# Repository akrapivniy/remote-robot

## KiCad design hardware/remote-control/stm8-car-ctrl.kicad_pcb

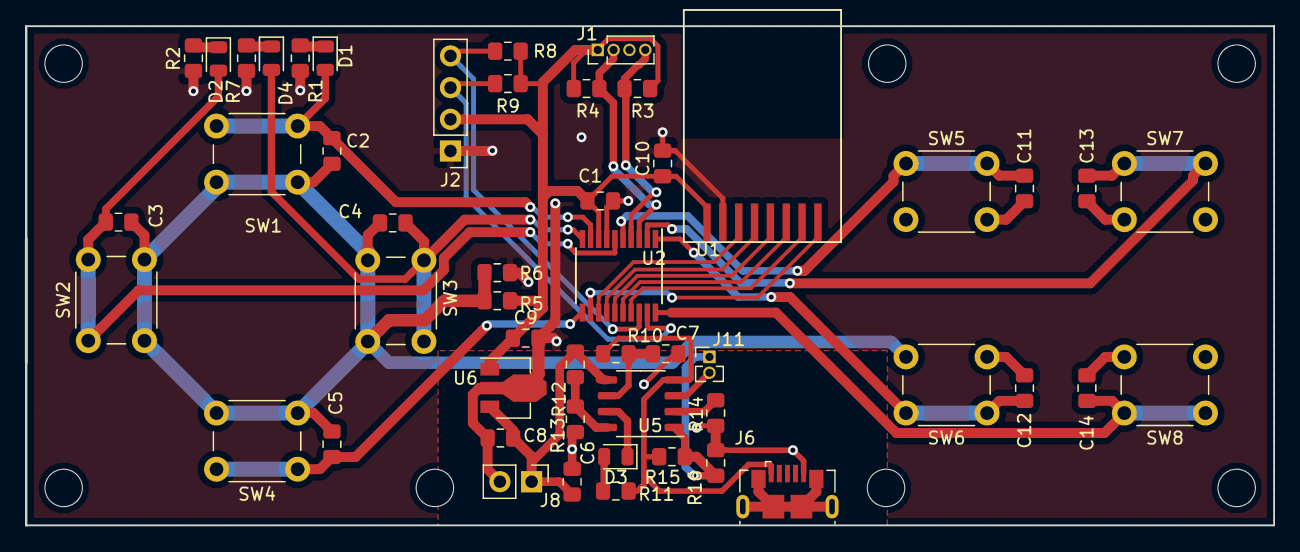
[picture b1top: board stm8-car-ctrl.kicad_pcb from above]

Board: 2 copper layers, 100.0 x 40.0 mm, 58 parts (0 on the bottom side), 32 nets.

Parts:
C1, C2, C3, C4, C5, C6, C7, C8, C9, C10, C11, C12, C13, C14: 100nF; C_0805_2012Metric_Pad1.15x1.40mm_HandSolder
D1, D2, D3, D4: LED; LED_0805_2012Metric
H1, H2, H3, H4, H6, H7, H8: MountingHole; MountingHole_3mm
J1: Prog; PinHeader_1x04_P1.27mm_Vertical
J2: I2C; PinHeader_1x04_P2.54mm_Vertical
J6: USB_B_Micro; USB_Micro-B_GCT_USB3076-30-A
J8: 3P BAT; PinHeader_1x02_P2.54mm_Vertical
J11: Temp; PinHeader_1x02_P1.27mm_Vertical
R1, R2, R7, R11, R15, R16: 1K; R_0805_2012Metric_Pad1.15x1.40mm_HandSolder
R3, R4, R12: 100K; R_0805_2012Metric_Pad1.15x1.40mm_HandSolder
R5, R6: 0; R_0805_2012Metric_Pad1.15x1.40mm_HandSolder
R8, R9: 4.7K; R_0805_2012Metric_Pad1.15x1.40mm_HandSolder
R10: 510K; R_0805_2012Metric_Pad1.15x1.40mm_HandSolder
R13: 150K-274K; R_0805_2012Metric_Pad1.15x1.40mm_HandSolder
R14: 2.4K; R_0805_2012Metric_Pad1.15x1.40mm_HandSolder
SW1, SW2, SW3, SW4, SW5, SW6, SW7, SW8: SW_Push; SW_PUSH_6mm_H8mm
U1: NRF24L; NRF24L01SMD
U2: STM8L051F3P; TSSOP-20_4.4x6.5mm_P0.65mm
U5: CN3085; SSOP-8_3.9x5.05mm_P1.27mm
U6: L78L33_SOT89; SOT-89-3

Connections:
+3V3: C1.1, C9.1, C10.1, J1.1, J2.2, R3.1, R4.1, R5.1, R8.1, R9.1, U1.1, U2.8, U6.1
+3V8: C6.1, C8.1, J8.1, R12.1, U5.5, U6.3
+5VD: J6.1, R10.1, R11.1, R15.2, U5.4
/Button0: C2.2, D1.2, SW1.1, U2.9
/Button1: C3.2, D2.2, SW2.1, U2.6
/Button2: C4.2, D4.2, SW3.1, U2.10
/Button3: C5.2, SW4.1, U2.11
/Button4: C11.2, SW5.1, U2.5
/Button5: C12.2, SW6.1, U2.1
/Button6: C13.2, SW7.1, U2.2
/Button7: C14.2, SW8.1, U2.20
/I2C_SCL: J2.3, R9.2, U2.19
/I2C_SDA: J2.4, R8.2, U2.18
/NRF_CE: U1.3, U2.13
/NRF_IRQ: U1.8, U2.12
/SPI_CLK: U1.5, U2.15
/SPI_CS: U1.4, U2.14
/SPI_MISO: U1.7, U2.17
/SPI_MOSI: U1.6, U2.16
/SWIM_DATA: J1.2, R4.2, U2.3
/SWIM_RESET: J1.4, R3.2, U2.4
GND: C1.2, C6.2, C7.2, C8.2, C9.2, C10.2, J1.3, J2.1, J6.5, J8.2, J11.2, R1.2, R2.2, R6.1, R7.2, R13.2, R14.2, R16.2, U1.2, U2.7, U5.3, U6.2
unnamed: C7.1, R10.2, U5.6
unnamed: C2.1, C3.1, C4.1, C5.1, C11.1, C12.1, C13.1, C14.1, R5.2, R6.2, SW1.2, SW2.2, SW3.2, SW4.2, SW5.2, SW6.2, SW7.2, SW8.2
unnamed: D1.1, R1.1
unnamed: D2.1, R2.1
unnamed: D3.1, U5.7
unnamed: D3.2, R11.2
unnamed: D4.1, R7.1
unnamed: J11.1, R15.1, R16.1, U5.1
unnamed: R12.2, R13.1, U5.8
unnamed: R14.1, U5.2

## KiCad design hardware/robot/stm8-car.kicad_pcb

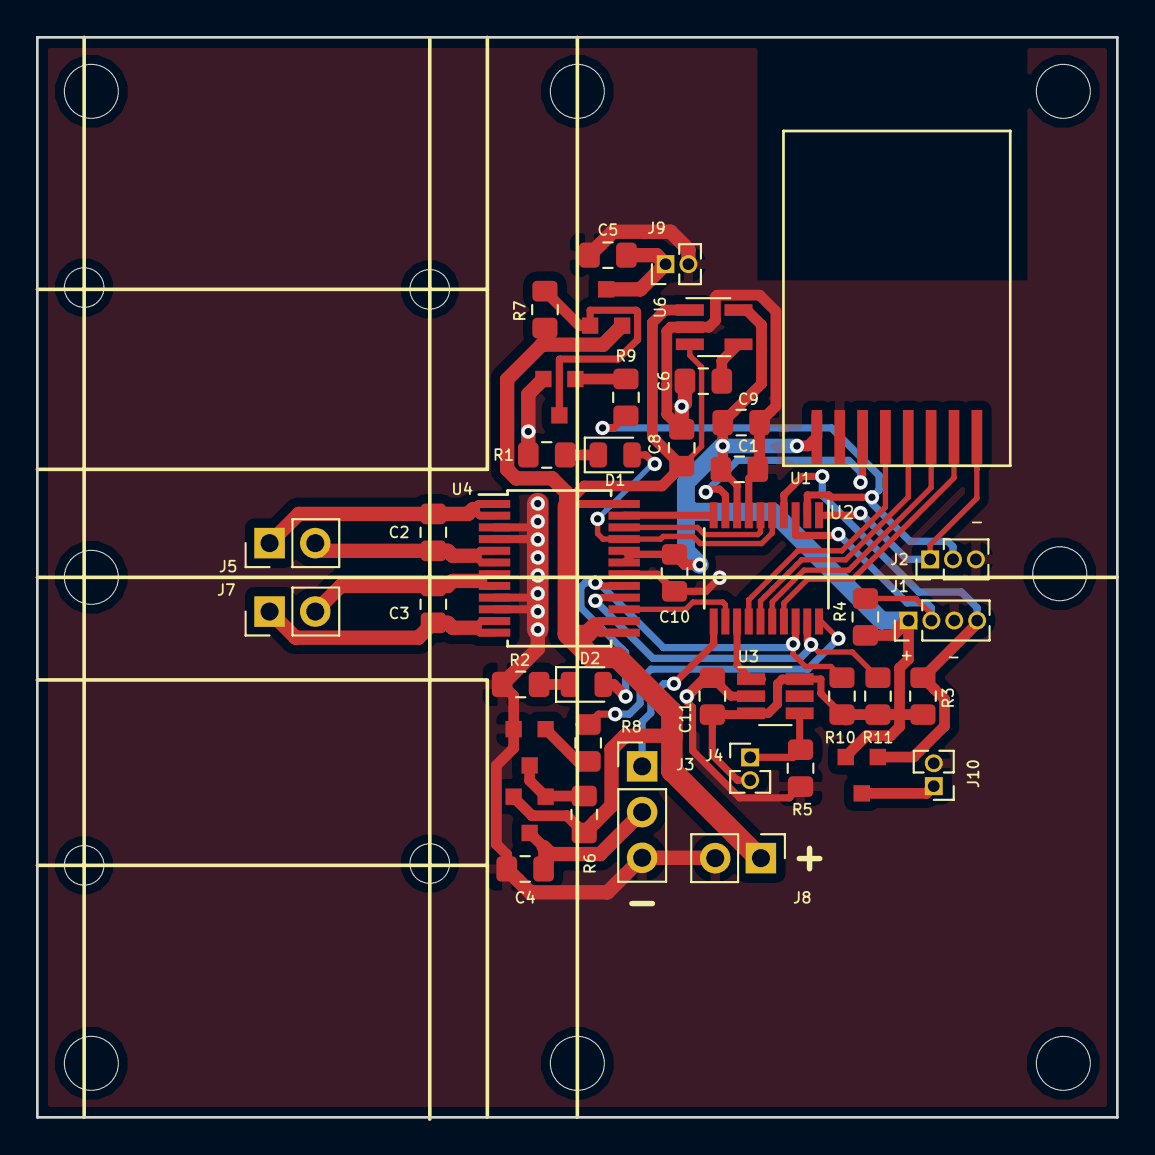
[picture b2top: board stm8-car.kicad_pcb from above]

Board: 2 copper layers, 60.0 x 60.0 mm, 54 parts (0 on the bottom side), 36 nets.

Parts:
C1, C6, C8, C9, C10, C11: 100nF; C_0805_2012Metric_Pad1.15x1.40mm_HandSolder
C2, C3, C4, C5: 0,1uF; C_0805_2012Metric_Pad1.15x1.40mm_HandSolder
D1, D2: LED; LED_0805_2012Metric
H1, H2, H3, H4, H5, H6, H7, H8: MountingHole; MountingHole_3mm
H9, H10, H11, H12: MountingHole; MountingHole_2.2mm_M2
J1: Prog; PinHeader_1x04_P1.27mm_Vertical
J2: UART; PinHeader_1x03_P1.27mm_Vertical
J3: SERVO; PinHeader_1x03_P2.54mm_Vertical
J4: DIODE; PinHeader_1x02_P1.27mm_Vertical
J5: MOTOR1; PinHeader_1x02_P2.54mm_Vertical
J7: MOTOR2; PinHeader_1x02_P2.54mm_Vertical
J8: 3P BAT; PinHeader_1x02_P2.54mm_Vertical
J9: DEVICE2; PinHeader_1x02_P1.27mm_Vertical
J10: DEVICE; PinHeader_1x02_P1.27mm_Vertical
Q1, Q2: BC847BLT1G; SOT23-3
R1, R2, R8, R9, R10, R11: 1K; R_0805_2012Metric_Pad1.15x1.40mm_HandSolder
R3, R4, R6, R7: 100K; R_0805_2012Metric_Pad1.15x1.40mm_HandSolder
R5: ?K; R_0805_2012Metric_Pad1.15x1.40mm_HandSolder
U1: NRF24L; NRF24L01SMD
U2: STM8L051F3P; TSSOP-20_4.4x6.5mm_P0.65mm
U3: INA181; SOT-23-6_Handsoldering
U4: TB6612FNG; SSOP-24_5.3x8.2mm_P0.65mm
U6: L78L33_SOT89; SOT-23-5_HandSoldering
VT1, VT2, VT3: NTS4101PT1G; SOT23-3

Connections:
+3V3: C1.1, C9.1, C10.1, C11.1, J1.1, J4.2, R3.1, R4.1, R10.1, R11.1, U1.1, U2.8, U3.3, U3.6, U4.19, U4.20, U6.5, VT3.2
+3V8: C8.1, J8.1, R6.1, R7.1, U4.13, U4.14, U4.24, U6.1, U6.3, VT1.2, VT2.2
/AIN1: D1.2, U2.5, U4.21
/AIN2: U2.6, U4.22
/BIN1: D2.2, R10.2, U2.18, U4.17
/BIN2: R11.2, U2.19, U4.16
/Device2Enable: J2.2, R9.2, U2.2
/Device2Power: C5.1, J9.1, VT2.3
/DeviceEnable: J1.4, R3.2, U2.4, VT3.1
/DevicePower: J10.1, VT3.3
/MotorA_PWM: U2.10, U4.23
/MotorB_PWM: U2.12, U4.15
/NRF_CE: U1.3, U2.9
/NRF_IRQ: J2.1, U1.8, U2.1
/SPI_CLK: U1.5, U2.15
/SPI_CS: U1.4, U2.14
/SPI_MISO: U1.7, U2.17
/SPI_MOSI: U1.6, U2.16
/SWIM_DATA: J1.2, R4.2, U2.3
/ServoEnable: R8.2, U2.20
/ServoPWM: J3.1, U2.11
/ServoPower: C4.1, J3.2, VT1.3
GND: C1.2, C4.2, C5.2, C6.2, C8.2, C9.2, C10.2, C11.2, J1.3, J2.3, J3.3, J8.2, J9.2, J10.2, Q1.2, Q2.2, R1.2, R2.2, R5.2, U1.2, U2.7, U3.2, U4.3, U4.4, U4.9, U4.10, U4.18, U6.2
unnamed: C2.1, J5.1, U4.1, U4.2
unnamed: C2.2, J5.2, U4.5, U4.6
unnamed: C3.1, J7.1, U4.11, U4.12
unnamed: C3.2, J7.2, U4.7, U4.8
unnamed: C6.1, U6.4
unnamed: D1.1, R1.1
unnamed: D2.1, R2.1
unnamed: J4.1, R5.1, U3.4
unnamed: Q1.1, R8.1
unnamed: Q1.3, R6.2, VT1.1
unnamed: Q2.1, R9.1
unnamed: Q2.3, R7.2, VT2.1
unnamed: U2.13, U3.1

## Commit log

2021-04-25 Init commit
